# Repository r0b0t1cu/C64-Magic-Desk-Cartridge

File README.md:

# C64 Magic Desk Cartridge

An open-source hardware clone of the **Magic Desk** cartridge format for the Commodore 64. Supports both **27C512** (64KB) and **29F040** (512KB) EPROMs/EEPROMs, with bank switching handled by a classic 74LS273 + 74LS02 glue logic combination.

This board is designed to be built with through-hole components and DIP sockets, making it easy to assemble, reprogram, and experiment with.

| Front | Back |
|-------|------|
|  |  |

---

## What is the Magic Desk Format?

Magic Desk is a simple and well-documented C64 cartridge format originally used by Commodore for titles like *Ghostbusters*, *Winter Games*, and others. It works by bank-switching 8KB ROM banks into the C64's memory map at `$8000`. A single byte write to `$DE00` selects the active bank; bit 7 controls the EXROM line to enable or disable the cartridge.
Because of its simplicity and wide software support, it became a popular format for homebrew multicarts and game compilations.

---

## Features

- Supports **27C512** (64KB) and **29F040** (512KB)
- Standard C64 cartridge edge connector
- DIP sockets for all ICs — easy to swap and reprogram
- PWR LED indicator
- RESET button
- Jumper configuration for ROM type

---

## Bill of Materials

| Ref | Qty | Value | Package |
|-----|-----|-------|---------|
| C1, C2, C3 | 3 | 100nF | Disc, 5.00mm pitch |
| R1 | 1 | 1K | Axial, horizontal |
| D1 | 1 | LED (PWR) | 3mm |
| U2 | 1 | 74LS273 | DIP-20, socket |
| U3 | 1 | 74LS02 | DIP-14, socket |
| U4 | 1 | 27C512 or 29F040 | DIP-32, socket |
| SW1 | 1 | RESET | Tactile push button 6mm |

---

## Jumper Configuration

The back of the board has a jumper table printed in silkscreen for quick reference. Configure the jumpers according to the ROM you are using:

### JD — default bank select (controls EXROM / cartridge enable)

| JD | Meaning |
|----|---------|
| X X=X | Cartridge always enabled |

### Address line jumpers (JF, JA16, JA17, JA18)

These select which address lines are connected, depending on the ROM size installed.

#### 27C512 (64KB)

| Jumper | Setting |
|--------|---------|
| JF | X X X |
| JA18 | X X X |
| JA17 | X=X X |
| JA16 | X X X |

#### 29F040 (512KB)

| Jumper | Setting |
|--------|---------|
| JF | X=X X |
| JA18 | X X=X |
| JA17 | X X=X |
| JA16 | X X=X |

> **[X=X]** means the two pads are bridged with a solder jumper or jumper cap. **[X X X]** means left open.

Refer to the silkscreen on the back of the board for the full table.

---

## ROM Images

This repository includes pre-compiled **512KB `.bin` files** ready to be burned directly to a **29F040** EEPROM. Each image is a Magic Desk format multicart containing a curated selection of C64 software.

```
roms/
└── *.bin    # Ready-to-burn 512KB images for 29F040
```

To burn a `.bin` file to a 29F040, use a programmer such as:
- TL866II Plus / T48 (xgecu)
- GQ-4X
- Any EPROM programmer that supports the 29F040

| Front | Back |
|-------|------|
|  |  |

---

## Creating Your Own ROM Image

Use the **Magic Desk Cartridge Generator** by Zzarko to build your own `.bin` files from `.prg` or `.crt` files:

- [Magic Desk Cartridge Generator V3.0](https://csdb.dk/release/?id=179083) — original release
- [Magic Desk Cartridge Generator V3.5](https://csdb.dk/release/?id=205274) — newer version (recommended)
- [Source on Bitbucket](https://bitbucket.org/zzarko/magic-desk-cartridge-generator/)

The generator creates a menu-driven launcher that lets you select titles directly on the C64, with no extra hardware needed.

---

If you enjoy my projects and would like to support my work, you can do so through PCBWay. You can also order the PCBs for this project directly from the link below. Every bit of support is appreciated!

<p>
  
  </a>
</p>

---

## Building the PCB

1. **Order the PCB** — use the Gerber files in `gerbers/`. Standard 2-layer 1.6mm FR4. JLCPCB, PCBWay, etc.
2. **Solder passives first** — capacitors, resistor, LED.
3. **Solder the edge connector** — take care with alignment; the card edge fingers go toward the bottom.
4. **Solder the DIP sockets** — do not solder ICs directly; use sockets so chips can be swapped.
5. **Configure jumpers** — set JF, JD, JA16, JA17, JA18 for your ROM type before inserting the chip.
6. **Insert ICs** — 74LS273, 74LS02, and your programmed EPROM/EEPROM.
7. **Insert into C64** — power on; the cartridge menu should appear immediately.

---

## Compatibility

Tested on:
- Commodore 64 (breadbin and short board)

Should work on:
- Commodore 64C
- Commodore 128 (in C64 mode)

---

## Related Projects

- [Magic Desk Cartridge Generator V3.5](https://csdb.dk/release/?id=205274) by Zzarko — the tool used to build the ROM images
- [Pi1541-Simple-HAT](https://github.com/r0b0t1cu/Pi1541-Simple-HAT) — Raspberry Pi HAT for Pi1541 disk emulation

---

## License

This project is open-source hardware released under the [CERN Open Hardware Licence v2 - Permissive (CERN-OHL-P)](https://ohwr.org/cern_ohl_p_v2.txt).

The Magic Desk Cartridge Generator is the work of Zzarko / Once Upon A Byte and is licensed separately.

---

## Author

Designed by [r0b0t1cu](https://github.com/r0b0t1cu) — 2026

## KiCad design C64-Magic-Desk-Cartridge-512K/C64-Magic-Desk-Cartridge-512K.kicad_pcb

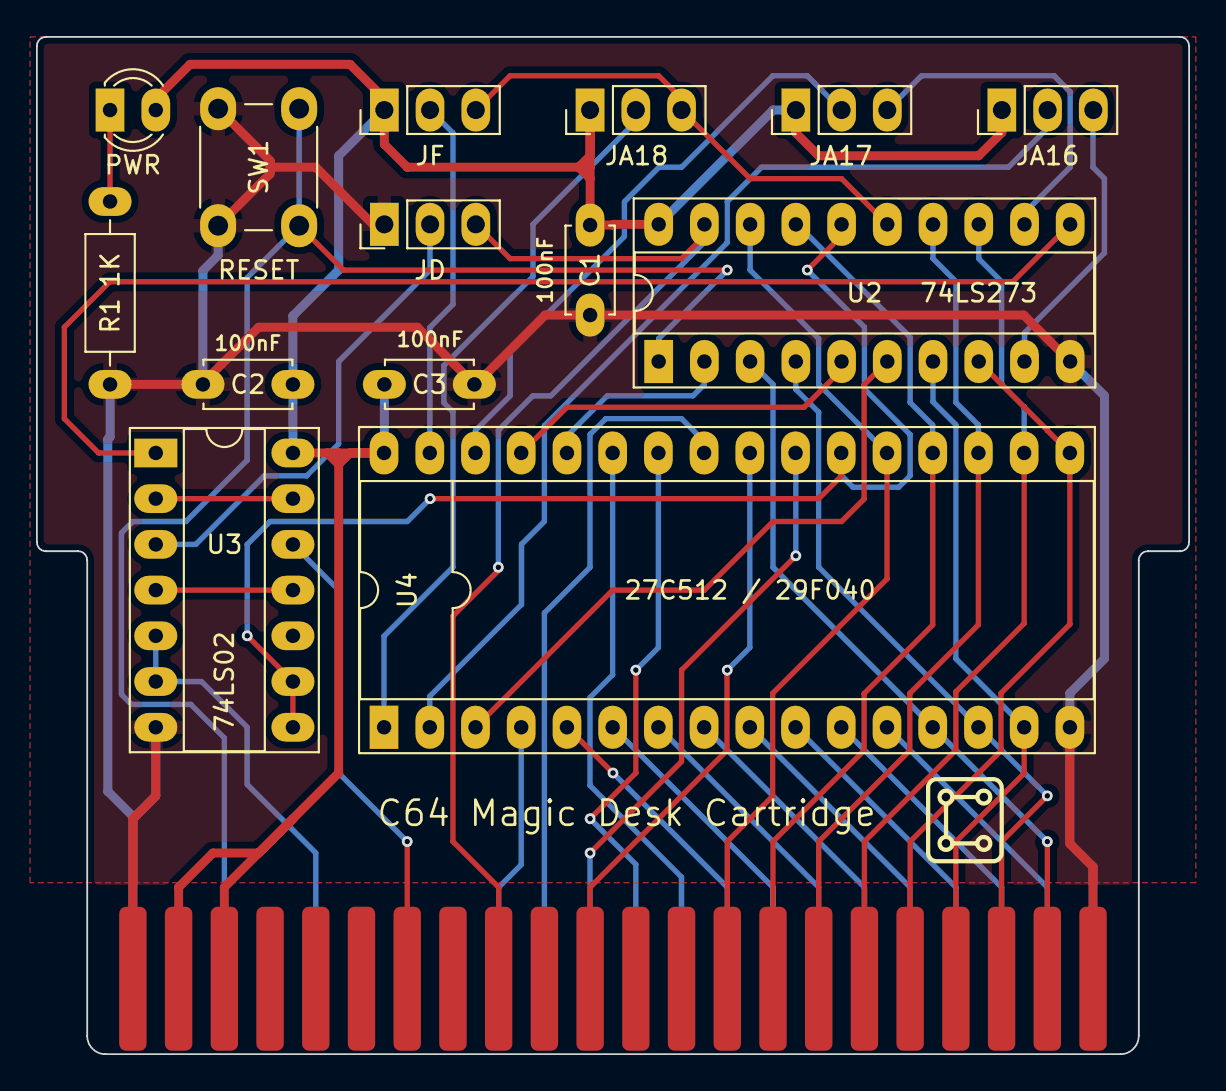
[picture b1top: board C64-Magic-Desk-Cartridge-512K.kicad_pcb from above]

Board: 2 copper layers, 64.0 x 56.5 mm, 15 parts (0 on the bottom side), 44 nets.

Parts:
C1, C2, C3: 100nF; C_Disc_D4.7mm_W2.5mm_P5.00mm
D1: PWR; LED_D3.0mm
JP1: JD; PinHeader_1x03_P2.54mm_Vertical
JP2: JA16; PinHeader_1x03_P2.54mm_Vertical
JP3: JA17; PinHeader_1x03_P2.54mm_Vertical
JP4: JA18; PinHeader_1x03_P2.54mm_Vertical
JP5: JF; PinHeader_1x03_P2.54mm_Vertical
R1: 1K; R_Axial_DIN0207_L6.3mm_D2.5mm_P10.16mm_Horizontal
SW1: RESET; SW_PUSH_6mm
U1: C64 Cartridge Edge Connector; C64_Cart_Edge
U2: 74LS273; DIP-20_W7.62mm_Socket_LongPads
U3: 74LS02; DIP-14_W7.62mm_Socket_LongPads
U4: 27C512 / 29F040; DIP-32_W15.24mm_Socket_LongPads

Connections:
/A0: U1.Y (A0), U4.12 (A0)
/A1: U1.X (A1), U4.11 (A1)
/A2: U1.W (A2), U4.10 (A2)
/A3: U1.V (A3), U4.9 (A3)
/A4: U1.U (A4), U4.8 (A4)
/A5: U1.T (A5), U4.7 (A5)
/A6: U1.S (A6), U4.6 (A6)
/A7: U1.R (A7), U4.5 (A7)
/A8: U1.P (A8), U4.27 (A8)
/A9: U1.N (A9), U4.26 (A9)
/A10: U1.M (A10), U4.23 (A10)
/A11: U1.L (A11), U4.25 (A11)
/A12: U1.K (A12), U4.4 (A12)
/CE: U2.16 (Q6), U3.8, U3.9, U4.22 (~CE)
/D0: U1.21 (D0), U2.3 (D0), U4.13 (DQ0)
/D1: U1.20 (D1), U2.4 (D1), U4.14 (DQ1)
/D2: U1.19 (D2), U2.7 (D2), U4.15 (DQ2)
/D3: U1.18 (D3), U2.8 (D3), U4.17 (DQ3)
/D4: U1.17 (D4), U2.13 (D4), U4.18 (DQ4)
/D5: U1.16 (D5), U2.14 (D5), U4.19 (DQ5)
/D6: U1.15 (D6), U2.17 (D6), U4.20 (DQ6)
/D7: U1.14 (D7), U2.18 (D7), U4.21 (DQ7)
/DIS: JP1.3 (B), U1.9 (_EXROM), U2.19 (Q7)
/EN: U2.11 (Cp), U3.1
/IO1: U1.7 (_IO1), U3.12
/J16: JP2.2 (C), U4.2 (A16)
/J17: JP3.2 (C), U4.30 (A17)
/J18: JP4.2 (C), U4.1 (A18)
/JWE: JP5.2 (C), U4.31 (~WE)
/PHI2: U1.E (PHI2), U3.5, U3.6
/RESET: SW1.1, U1.C (_RESET), U2.1 (~Mr)
/ROML: U1.11 (_ROML), U4.24 (~OE)
/S13: U2.2 (Q0), U4.28 (A13)
/S14: U2.5 (Q1), U4.29 (A14)
/S15: U2.6 (Q2), U4.3 (A15)
/S16: JP2.3 (B), U2.9 (Q3)
/S17: JP3.3 (B), U2.12 (Q4)
/S18: JP4.3 (B), JP5.3 (B), U2.15 (Q5)
GND: C1.2, C2.2, C3.2, JP1.1 (A), R1.1, SW1.2, U1.1 (GND), U1.22 (GND), U1.A (GND), U1.Z (GND), U2.10 (GND), U3.7 (GND), U4.16 (GND)
unnamed: D1.1 (K), R1.2
unnamed: JP1.2 (C), U3.3
unnamed: U3.4, U3.11
unnamed: U3.2, U3.13
VCC: C1.1, C2.1, C3.1, D1.2 (A), JP2.1 (A), JP3.1 (A), JP4.1 (A), JP5.1 (A), U1.2 (+5V), U1.3 (+5V), U2.20 (VCC), U3.14 (VCC), U4.32 (VCC)
